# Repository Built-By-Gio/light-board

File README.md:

# Light Board ("World Saving LEDs")

My first custom PCB: a Simon Says game. Seven colored LEDs, seven buttons, a passive piezo buzzer and a slide switch sit on a 98 × 86 mm two-layer through-hole board, run by a socketed Arduino Nano. The board lights a growing sequence and you repeat it on the buttons.

This repo also holds an earlier, separate layout, the 7-channel 9V LED board (`hardware/led-9v-controller/`). It has no microcontroller and is described in its own section below.

Built by Gio ([Built-By-Gio](https://github.com/Built-By-Gio)).

## Status (2026-11-25)

Light Board (Simon Says):

- Built: boards were made by JLCPCB from the gerbers in `hardware/` (dated 2026-09-22) and hand-soldered. The assembled board plays Simon Says, with a few issues I still need to write up. There is no photo of the board in this repo yet.
- Firmware: the original game sketch was lost. `firmware/simon_says/simon_says.ino` is a replacement written to match the pin labels printed on the silkscreen. It compiles for the Arduino Nano (2026-11-25, arduino-cli 1.5.1 and the arduino:avr 1.8.8 core: 4188 bytes of flash, 112 bytes of RAM). It runs on the assembled board.
- Design source: the KiCad layout is in `hardware/kicad/` (`light_board.kicad_pcb` and `light_board.kicad_pro`). It is the same layout as the gerbers I ordered: same 98 × 86 mm outline, same 91 plated holes (positions and sizes), same pad positions and the same trace routing on both copper layers. This file was saved on 2026-09-22, a few hours before the ordered gerbers were made, and the ordered gerbers differ in these details: traces are 0.4 mm wide instead of 0.3 mm, the button pads are 1.8 mm instead of 1.7 mm, the slide-switch pads are 2.0 mm instead of 1.8 mm, the four mounting holes sit 5 mm from the corners instead of 3.5 mm, and the silkscreen uses a different font and leaves out the reference designators (D1, R1, S1 and so on). The bottom ground fill is defined in the file but saved unfilled; refill zones in KiCad (Edit → Fill All Zones) before plotting. With the zones refilled, KiCad 10's design-rule check (2026-11-25) gives 0 errors and 0 unconnected items, plus 101 warnings that are all silkscreen placement or footprint-library notes.
- There is no schematic file yet.

7-channel 9V LED board:

- I ordered and built an earlier version of this board.
- The layout file in this repo was corrected on 2026-11-25. Channels 2 to 5 moved right by 2, 4, 6 and 8 mm, because in the old file each switch's GND pad sat on the next resistor's +9V pad in four places (a short across the supply). The LED pads went from 2.5 mm to 2.0 mm. The second row (D6, D7) is now wired to J1. The board size (160 × 70 mm, 2 layers), parts, values, reference designators and color labels are unchanged.
- The corrected file passes KiCad 10's design-rule check with 0 errors and 0 unconnected items (59 warnings, all silkscreen-over-copper or footprint-library notes).
- The corrected version is not ordered yet.

Still to add:

- Photo of the soldered board
- Demo video
- Write-up of the known issues
- Schematic for the Light Board

## What you need

### Light Board parts

There is no BOM file. This table comes from the gerber and drill files in `hardware/gerbers/`: part labels and values from the top silkscreen, hole sizes and spacing from `lightboard-PTH.TXT`.

| Part | Qty | Silkscreen label | Holes (from the drill file) |
|---|---|---|---|
| Arduino Nano | 1 | "ARDUINO NANO", "USB THIS END" | 2 rows of 15, 1.0 mm, 2.54 mm pitch, rows 15.24 mm apart |
| 1×15 female header (socket for the Nano) | 2 | none | same as above |
| 5 mm LED | 7 | RED D9, BLUE D8, ORANGE D7, YELLOW D6, GREEN D5, WHITE D4, RED D3 | 2 per LED, 0.9 mm, 2.54 mm apart |
| 470 Ω resistor, axial | 7 | "470" under each LED | 2 per resistor, 0.8 mm, 7.62 mm apart |
| 4-pin tactile push button | 7 | S1 D12, S2 D11, S3 D10, S4 A3, S5 A2, S6 A1, S7 A0 | 4 per button, 1.0 mm, on a 6.5 × 4.5 mm rectangle |
| Passive piezo buzzer | 1 | "BUZZER D2", "+" mark | 2, 1.0 mm, 7.6 mm apart |
| 3-pin slide switch | 1 | "PWR SW (A4)", "GND" | 3, 1.2 mm, 2.54 mm pitch |

"Passive" for the buzzer comes from the firmware, which drives it with `tone()` at a different pitch for each LED. The Nano socket is how the original board was built; you can also solder the Nano directly.

How the parts connect (traced from the copper layers):

| Part | Nano pin | Circuit |
|---|---|---|
| LEDs, left to right | D9, D8, D7, D6, D5, D4, D3 | pin → LED ("+" pad) → 470 Ω → GND |
| Buttons S1 to S7 | D12, D11, D10, A3, A2, A1, A0 | pin → button → GND (uses the Nano's internal pull-ups) |
| Buzzer | D2 | pin → buzzer "+" → GND |
| Slide switch | A4 | middle pin to A4, the pin next to "GND" to ground, third pin unconnected |

The bottom layer is a ground fill. The Nano's 5V and VIN pins are not connected to anything on the board, so the board is powered through the Nano's USB port. The slide switch does not cut power; it is an input that the sketch reads on A4.

### Tools and software

- Soldering iron and solder for through-hole parts
- Arduino IDE 2.x or arduino-cli, with the "Arduino AVR Boards" core (tested to compile with 1.8.8)
- USB cable for the Nano
- No extra libraries are needed

## How to build and run

1. Order the board. Upload `hardware/lightboard-gerbers.zip` to a PCB maker (the original boards came from JLCPCB). Settings from the files: 2 layers, 98 × 86 mm outline. The drill file uses 0.8, 0.9, 1.0 and 1.2 mm plated holes (91 in total) plus four 3.2 mm unplated mounting holes, 5 mm in from each corner. Board thickness, color and finish are not specified in the files; use the maker's defaults or your choice.
2. Get the parts in the table above.
3. Solder the parts where the silkscreen shows them. Put each LED's long leg (anode) in the pad marked "+". Mount the Nano (or its sockets) with the USB connector at the "USB THIS END" mark.
4. Open `firmware/simon_says/simon_says.ino` in the Arduino IDE. Pick Tools → Board → Arduino Nano and Processor → ATmega328P. If the upload fails on a clone Nano, try Processor → ATmega328P (Old Bootloader). Upload.
   With arduino-cli: `arduino-cli compile --fqbn arduino:avr:nano firmware/simon_says` then `arduino-cli upload -p <port> --fqbn arduino:avr:nano firmware/simon_says`.
5. Power the Nano over USB and slide the switch to the side that connects A4 to GND. If the game only runs with the switch the other way, flip the test in `on()` at the top of the sketch.

How the game plays (from the sketch):

- With the switch on, the LEDs sweep left to right and back with a tone for each one.
- Each round the board adds one random LED to the sequence and plays the whole sequence. Each LED has its own note (C4 to B4). The playback speeds up each round, down to 150 ms per step.
- Repeat the sequence on the buttons. Each button lights its LED and plays its note while held.
- A wrong button, or no press within 3 seconds, ends the game: all LEDs light with a low tone, then the LEDs blink once per round you completed (your score). A new game starts after that.
- Completing 50 rounds plays a win flash and starts over.
- Sliding the switch off turns everything off and resets the game.

## The 7-channel 9V LED board (earlier layout)

A separate, earlier design in `hardware/led-9v-controller/`: seven independent channels, each +9V → 370 Ω resistor → 5 mm LED → switch → GND, fed from a 2-pin screw terminal. There is no microcontroller. Board outline 160 × 70 mm, 2 layers, through-hole. I ordered and built an earlier version of this board; the corrected layout here (see the Status section) is not ordered yet. Gerber and drill files exported from the corrected layout are in `hardware/led-9v-controller/gerbers/`.

Two things to know before ordering:

- The file has no solder-mask layers, so the gerbers include no mask files.
- The bar on each LED outline sits on the anode (resistor) side. Place each LED with its long leg (anode) toward the resistor, as the silkscreen note says, not by the bar.

Parts, from the footprints and values in `LED_9V_Controller.kicad_pcb`:

| Reference | Part | Qty | Footprint in the file |
|---|---|---|---|
| J1 | 2-pin screw terminal, 9V input | 1 | 5.08 mm pitch, 1.5 mm holes |
| R1 to R7 | 370 Ω resistor, axial | 7 | 7.62 mm pitch, 1.0 mm holes |
| D1 to D7 | 5 mm LED: red, blue, orange, yellow, green, white, red | 7 | 2.54 mm pitch, 1.0 mm holes |
| S1 to S7 | 2-pin switch (or wires to an external switch) | 7 | 6 mm pitch, 1.1 mm holes |

370 Ω is not a common stock value; 360 Ω and 390 Ω are the nearest common ones. More notes are in `hardware/led-9v-controller/README.txt`. Open `LED_9V_Controller.kicad_pro` in KiCad to edit it.

## Repo layout

| Path | What it is |
|---|---|
| `firmware/simon_says/simon_says.ino` | Simon Says game for the Light Board |
| `firmware/README.md` | Short flashing notes |
| `hardware/lightboard-gerbers.zip` | Light Board gerber and drill files, ready to upload to a PCB maker |
| `hardware/gerbers/` | The same 8 files, unzipped (copper, mask, silkscreen, outline, drill) |
| `hardware/kicad/` | Light Board KiCad project and layout (`light_board.kicad_pro`, `light_board.kicad_pcb`) |
| `hardware/led-9v-controller/` | The earlier 7-channel 9V LED board: KiCad project, corrected layout and notes |
| `hardware/led-9v-controller/gerbers/` | Gerber and drill files exported from the corrected 9V layout |
| `media/silkscreen_from_gerbers.png` | Image of the Light Board's top silkscreen, top copper and outline, rendered from the gerbers |
| `media/led-9v-board-top.svg` | Top copper and silkscreen of the corrected 9V board |

## Roadmap / future plans

- Write down the known issues on the assembled board and what fixes them
- Photograph the soldered board and record a demo video
- Recover or redraw the Light Board schematic

## Credits and license

I designed and built both boards. Released under the MIT License; see `LICENSE`.

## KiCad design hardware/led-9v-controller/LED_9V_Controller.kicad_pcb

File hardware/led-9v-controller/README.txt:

7-CHANNEL 9V LED PCB
=====================

This board is laid out from the supplied schematic as seven independent 9V LED channels.
Each channel is:
    +9V -> 370 ohm resistor -> LED -> switch -> GND

Parts to solder:
- J1: 2-pin screw terminal for 9V input
- R1-R7: 370 ohm through-hole resistors
- D1-D7: 5mm through-hole LEDs
- S1-S7: 2-pin external switches (or wire your own switches to the two pads)

LED colors on the silkscreen:
D1 RED
D2 BLUE
D3 ORANGE
D4 YELLOW
D5 GREEN
D6 WHITE
D7 RED

IMPORTANT:
The supplied schematic has the final LED/switch return (the D2/S7 section) on named nets
rather than explicitly returning to BAT1-. To make the physical board function as a normal
7-channel LED board, S7's return is connected to GND like the other six channels.

The 370 ohm resistors are retained from the supplied schematic.
Check your LED polarity before soldering: the LED anode (+ / long leg) goes toward the resistor;
the cathode (- / short leg / flat side) goes toward the switch.

Board size: 160 mm x 70 mm
Copper: 2 layer
Through-hole components

Open LED_9V_Controller.kicad_pcb in KiCad PCB Editor. Before ordering, run ERC/DRC and verify
the exact footprints and manufacturer design rules you want to use.

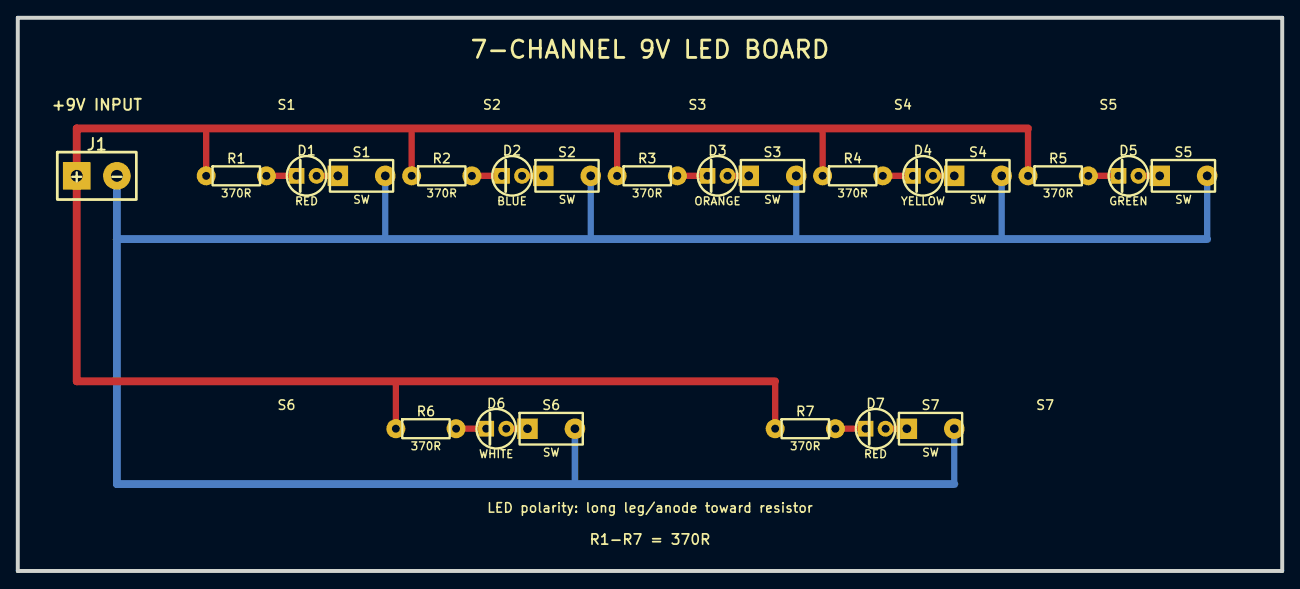
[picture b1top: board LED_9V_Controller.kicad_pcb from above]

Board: 2 copper layers, 160.0 x 70.0 mm, 22 parts (0 on the bottom side), 16 nets.

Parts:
D1, D7: RED; LED_5mm
D2: BLUE; LED_5mm
D3: ORANGE; LED_5mm
D4: YELLOW; LED_5mm
D5: GREEN; LED_5mm
D6: WHITE; LED_5mm
J1: 9V; TERM_2P_5.08
R1, R2, R3, R4, R5, R6, R7: 370R; R_Axial_P7.62
S1, S2, S3, S4, S5, S6, S7: SW; SW_2P

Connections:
+9V: J1.1, R1.1, R2.1, R3.1, R4.1, R5.1, R6.1, R7.1
GND: J1.2, S1.2, S2.2, S3.2, S4.2, S5.2, S6.2, S7.2
LED1_A: D1.1, R1.2
LED2_A: D2.1, R2.2
LED3_A: D3.1, R3.2
LED4_A: D4.1, R4.2
LED5_A: D5.1, R5.2
LED6_A: D6.1, R6.2
LED7_A: D7.1, R7.2
SW1_LED: D1.2, S1.1
SW2_LED: D2.2, S2.1
SW3_LED: D3.2, S3.1
SW4_LED: D4.2, S4.1
SW5_LED: D5.2, S5.1
SW6_LED: D6.2, S6.1
SW7_LED: D7.2, S7.1

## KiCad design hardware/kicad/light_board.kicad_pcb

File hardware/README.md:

- `gerbers/` + `lightboard-gerbers.zip`: the Light Board (Simon Says) files sent to JLCPCB (Sep 22 2026). Both hold the same 8 files.
- `kicad/`: the Light Board KiCad project (`light_board.kicad_pro`) and layout (`light_board.kicad_pcb`). It is the same layout as the ordered gerbers: same outline, holes, pad positions and trace routing. The ordered gerbers have 0.4 mm traces (0.3 mm in this file), 1.8 mm button pads (1.7 mm), 2.0 mm slide-switch pads (1.8 mm), mounting holes 5 mm from the corners (3.5 mm), and a silkscreen with a different font and no reference designators. The bottom ground fill is saved unfilled; refill zones before plotting. With zones refilled, KiCad 10's design-rule check gives 0 errors and 0 unconnected items. There is no schematic file yet.
- `led-9v-controller/`: an earlier board, 7 LED channels on 9V with plain switches and no microcontroller. KiCad project (`.kicad_pro`), layout (`.kicad_pcb`) and exported gerbers and drill file (`gerbers/`); there is no schematic file. I ordered and built an earlier version of this board. The layout was corrected on 2026-11-25 (channels 2 to 5 moved apart to remove four +9V-to-GND pad overlaps, LED pads 2.5 → 2.0 mm, second row wired to J1) and passes KiCad 10's design-rule check with 0 errors and 0 unconnected items. The corrected version is not ordered yet. The file has no solder-mask layers, and the LED outline's bar sits on the anode side, so place LEDs with the anode toward the resistor.

Still to add:

- Schematic for the Light Board

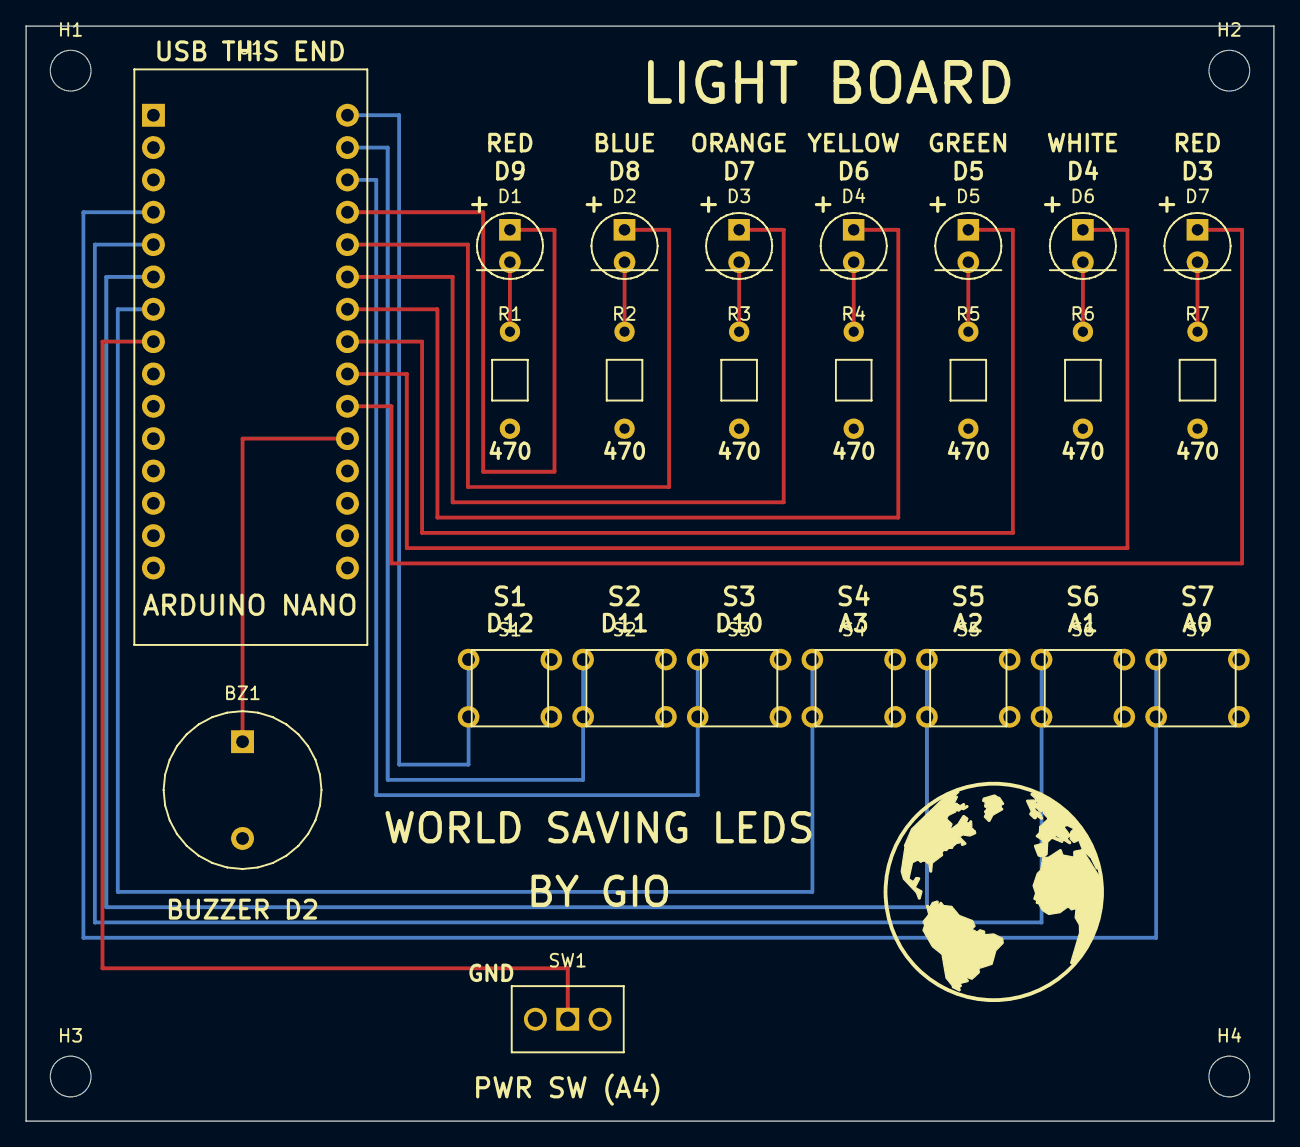
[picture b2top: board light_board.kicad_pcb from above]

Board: 2 copper layers, 98.0 x 86.0 mm, 28 parts (0 on the bottom side), 24 nets.

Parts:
BZ1: BUZZER_PASSIVE; BZ1
D1: LED_RED; D1
D2: LED_BLUE; D2
D3: LED_ORANGE; D3
D4: LED_YELLOW; D4
D5: LED_GREEN; D5
D6: LED_WHITE; D6
D7: LED_RED; D7
H1, H2, H3, H4: M3; MountingHole
R1: 470; R1
R2: 470; R2
R3: 470; R3
R4: 470; R4
R5: 470; R5
R6: 470; R6
R7: 470; R7
S1: SW_PUSH_6mm; S1
S2: SW_PUSH_6mm; S2
S3: SW_PUSH_6mm; S3
S4: SW_PUSH_6mm; S4
S5: SW_PUSH_6mm; S5
S6: SW_PUSH_6mm; S6
S7: SW_PUSH_6mm; S7
SW1: SLIDE_SPDT; SW1
U1: Arduino_Nano; U1

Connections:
A0: S7.1, S7.2, U1.4
A1: S6.1, S6.2, U1.5
A2: S5.1, S5.2, U1.6
A3: S4.1, S4.2, U1.7
A4: SW1.2, U1.8
D2: BZ1.1, U1.26
D3: D7.1, U1.25
D4: D6.1, U1.24
D5: D5.1, U1.23
D6: D4.1, U1.22
D7: D3.1, U1.21
D8: D2.1, U1.20
D9: D1.1, U1.19
D10: S3.1, S3.2, U1.18
D11: S2.1, S2.2, U1.17
D12: S1.1, S1.2, U1.16
GND: BZ1.2, R1.2, R2.2, R3.2, R4.2, R5.2, R6.2, R7.2, S1.3, S1.4, S2.3, S2.4, S3.3, S3.4, S4.3, S4.4, S5.3, S5.4, S6.3, S6.4, S7.3, S7.4, SW1.1, U1.14, U1.27
L0: D1.2, R1.1
L1: D2.2, R2.1
L2: D3.2, R3.1
L3: D4.2, R4.1
L4: D5.2, R5.1
L5: D6.2, R6.1
L6: D7.2, R7.1
